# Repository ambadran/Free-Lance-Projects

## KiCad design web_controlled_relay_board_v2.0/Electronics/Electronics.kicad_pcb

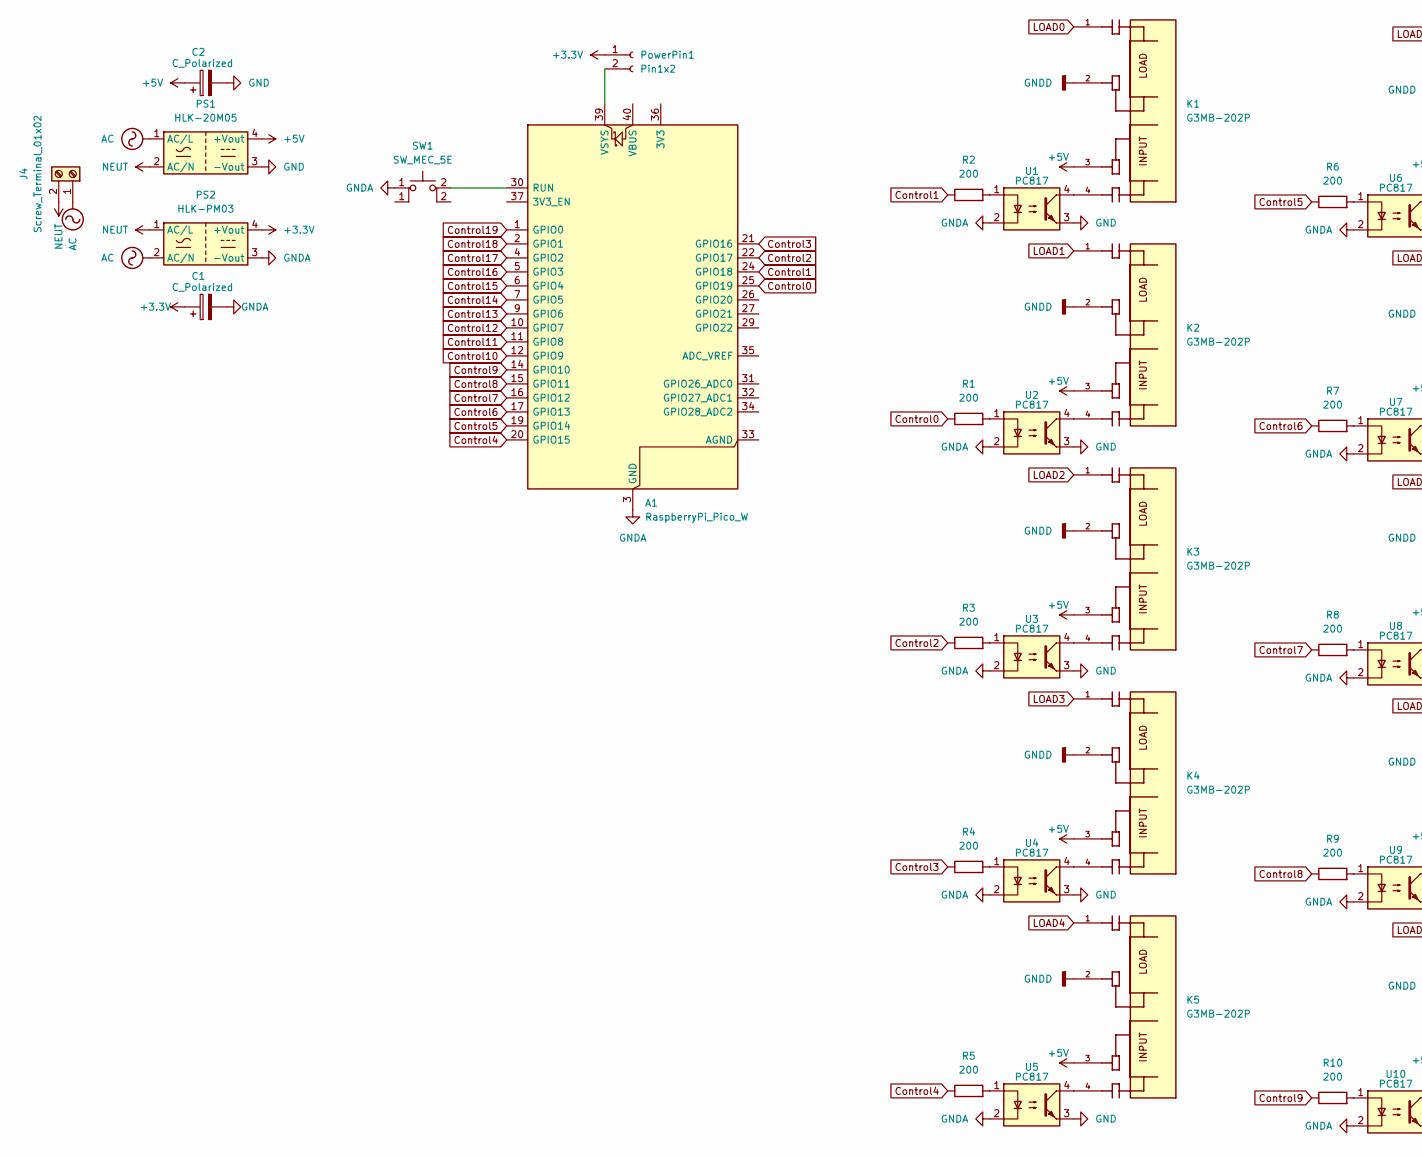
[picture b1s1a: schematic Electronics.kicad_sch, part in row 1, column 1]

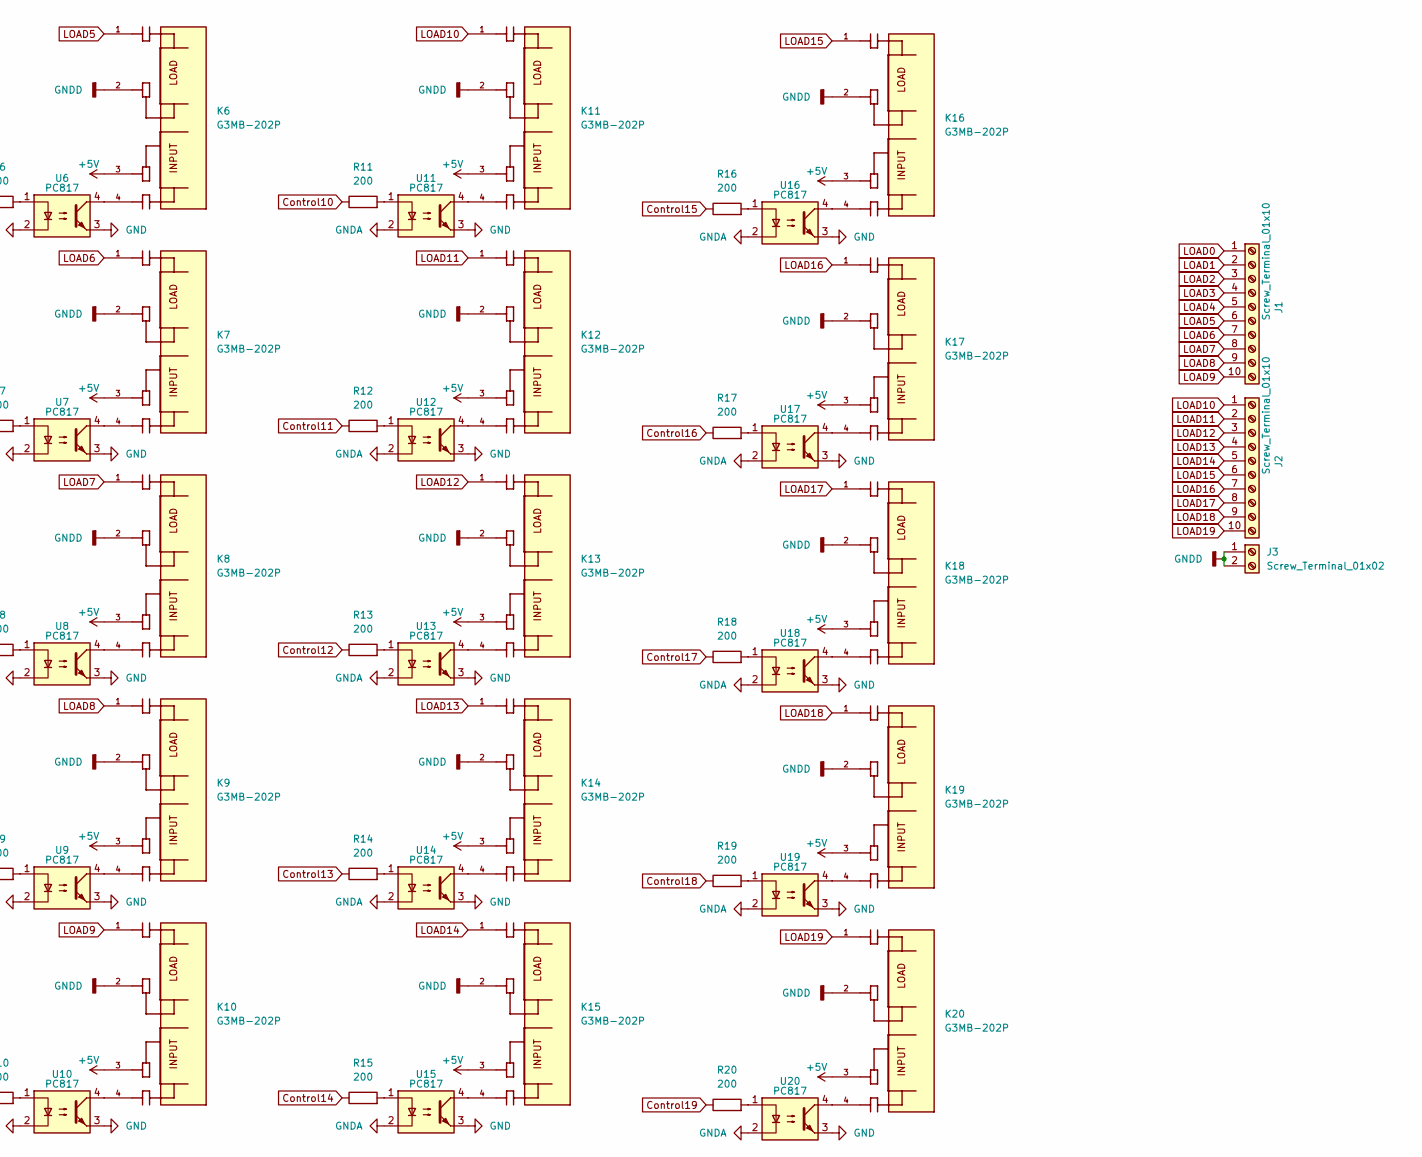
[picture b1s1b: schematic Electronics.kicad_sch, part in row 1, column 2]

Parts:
A1: RaspberryPi_Pico_W; RaspberryPi_Pico_Common_THT
C1: C_Polarized; CP_Radial_D6.3mm_P2.50mm
C2: C_Polarized; CP_Radial_D8.0mm_P3.50mm
J1, J2: Screw_Terminal_01x10; TerminalBlock_CUI_TB007-508-10_1x10_P5.08mm_Horizontal
J3, J4: Screw_Terminal_01x02; TerminalBlock_bornier-2_P5.08mm
K1, K2, K3, K4, K5, K6, K7, K8, K9, K10, K11, K12, K13, K14, K15, K16, K17, K18, K19, K20: G3MB-202P; RELAY_G3MB-202P; PARTREV J091-E1-1A
PS1: HLK-20M05; Converter_ACDC_Hi-Link_HLK-20Mxx
PS2: HLK-PM03; Converter_ACDC_Hi-Link_HLK-PMxx
PowerPin1: Pin1x2; PinSocket_1x02_P2.54mm_Vertical
R1, R2, R3, R4, R5, R6, R7, R8, R9, R10, R11, R12, R13, R14, R15, R16, R17, R18, R19, R20: 200; R_Axial_DIN0207_L6.3mm_D2.5mm_P7.62mm_Horizontal
SW1: SW_MEC_5E; SW_PUSH_6mm
U1, U2, U3, U4, U5, U6, U7, U8, U9, U10, U11, U12, U13, U14, U15, U16, U17, U18, U19, U20: PC817; DIP-4_W7.62mm

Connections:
+3.3V: C1.1, PS2.4 (+Vout), PowerPin1.1
+5V: C2.1, K1.3, K2.3, K3.3, K4.3, K5.3, K6.3, K7.3, K8.3, K9.3, K10.3, K11.3, K12.3, K13.3, K14.3, K15.3, K16.3, K17.3, K18.3, K19.3, K20.3, PS1.4 (+Vout)
AC: J4.1, PS1.1 (AC/L), PS2.2 (AC/N)
Control0: A1.25 (GPIO19), R1.1
Control1: A1.24 (GPIO18), R2.1
Control2: A1.22 (GPIO17), R3.1
Control3: A1.21 (GPIO16), R4.1
Control4: A1.20 (GPIO15), R5.1
Control5: A1.19 (GPIO14), R6.1
Control6: A1.17 (GPIO13), R7.1
Control7: A1.16 (GPIO12), R8.1
Control8: A1.15 (GPIO11), R9.1
Control9: A1.14 (GPIO10), R10.1
Control10: A1.12 (GPIO9), R11.1
Control11: A1.11 (GPIO8), R12.1
Control12: A1.10 (GPIO7), R13.1
Control13: A1.9 (GPIO6), R14.1
Control14: A1.7 (GPIO5), R15.1
Control15: A1.6 (GPIO4), R16.1
Control16: A1.5 (GPIO3), R17.1
Control17: A1.4 (GPIO2), R18.1
Control18: A1.2 (GPIO1), R19.1
Control19: A1.1 (GPIO0), R20.1
GND: C2.2, PS1.3 (-Vout), U1.3, U2.3, U3.3, U4.3, U5.3, U6.3, U7.3, U8.3, U9.3, U10.3, U11.3, U12.3, U13.3, U14.3, U15.3, U16.3, U17.3, U18.3, U19.3, U20.3
GNDA: A1.3 (GND), A1.8 (GND), A1.13 (GND), A1.18 (GND), A1.23 (GND), A1.28 (GND), A1.38 (GND), C1.2, PS2.3 (-Vout), SW1.1, U1.2, U2.2, U3.2, U4.2, U5.2, U6.2, U7.2, U8.2, U9.2, U10.2, U11.2, U12.2, U13.2, U14.2, U15.2, U16.2, U17.2, U18.2, U19.2, U20.2
GNDD: J3.1, J3.2, K1.2, K2.2, K3.2, K4.2, K5.2, K6.2, K7.2, K8.2, K9.2, K10.2, K11.2, K12.2, K13.2, K14.2, K15.2, K16.2, K17.2, K18.2, K19.2, K20.2
LOAD0: J1.1, K1.1
LOAD1: J1.2, K2.1
LOAD2: J1.3, K3.1
LOAD3: J1.4, K4.1
LOAD4: J1.5, K5.1
LOAD5: J1.6, K6.1
LOAD6: J1.7, K7.1
LOAD7: J1.8, K8.1
LOAD8: J1.9, K9.1
LOAD9: J1.10, K10.1
LOAD10: J2.1, K11.1
LOAD11: J2.2, K12.1
LOAD12: J2.3, K13.1
LOAD13: J2.4, K14.1
LOAD14: J2.5, K15.1
LOAD15: J2.6, K16.1
LOAD16: J2.7, K17.1
LOAD17: J2.8, K18.1
LOAD18: J2.9, K19.1
LOAD19: J2.10, K20.1
NEUT: J4.2, PS1.2 (AC/N), PS2.1 (AC/L)
unnamed: A1.30 (RUN), SW1.2
unnamed: A1.39 (VSYS), PowerPin1.2
unnamed: K1.4, U1.4
unnamed: K2.4, U2.4
unnamed: K3.4, U3.4
unnamed: K4.4, U4.4
unnamed: K5.4, U5.4
unnamed: K6.4, U6.4
unnamed: K7.4, U7.4
unnamed: K8.4, U8.4
unnamed: K9.4, U9.4
unnamed: K10.4, U10.4
unnamed: K11.4, U11.4
unnamed: K12.4, U12.4
unnamed: K13.4, U13.4
unnamed: K14.4, U14.4
unnamed: K15.4, U15.4
unnamed: K16.4, U16.4
unnamed: K17.4, U17.4
unnamed: K18.4, U18.4
unnamed: K19.4, U19.4
unnamed: K20.4, U20.4
unnamed: R1.2, U2.1
unnamed: R2.2, U1.1
unnamed: R3.2, U3.1
unnamed: R4.2, U4.1
unnamed: R5.2, U5.1
unnamed: R6.2, U6.1
unnamed: R7.2, U7.1
unnamed: R8.2, U8.1
unnamed: R9.2, U9.1
unnamed: R10.2, U10.1
unnamed: R11.2, U11.1
unnamed: R12.2, U12.1
unnamed: R13.2, U13.1
unnamed: R14.2, U14.1
unnamed: R15.2, U15.1
unnamed: R16.2, U16.1
unnamed: R17.2, U17.1
unnamed: R18.2, U18.1
unnamed: R19.2, U19.1
unnamed: R20.2, U20.1

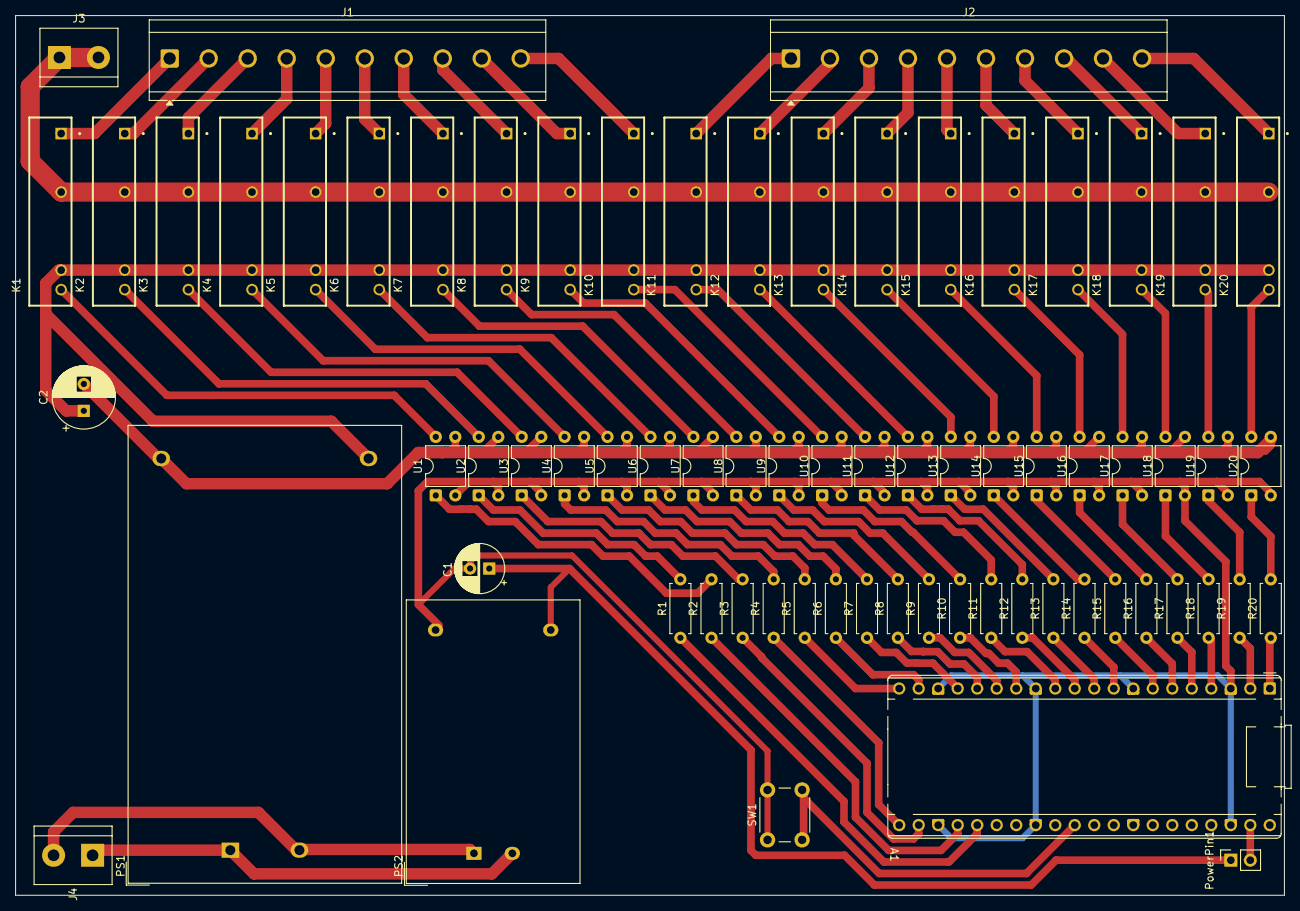
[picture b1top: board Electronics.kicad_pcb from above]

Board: 2 copper layers, 165.2 x 114.6 mm, 71 parts (0 on the bottom side), 89 nets.

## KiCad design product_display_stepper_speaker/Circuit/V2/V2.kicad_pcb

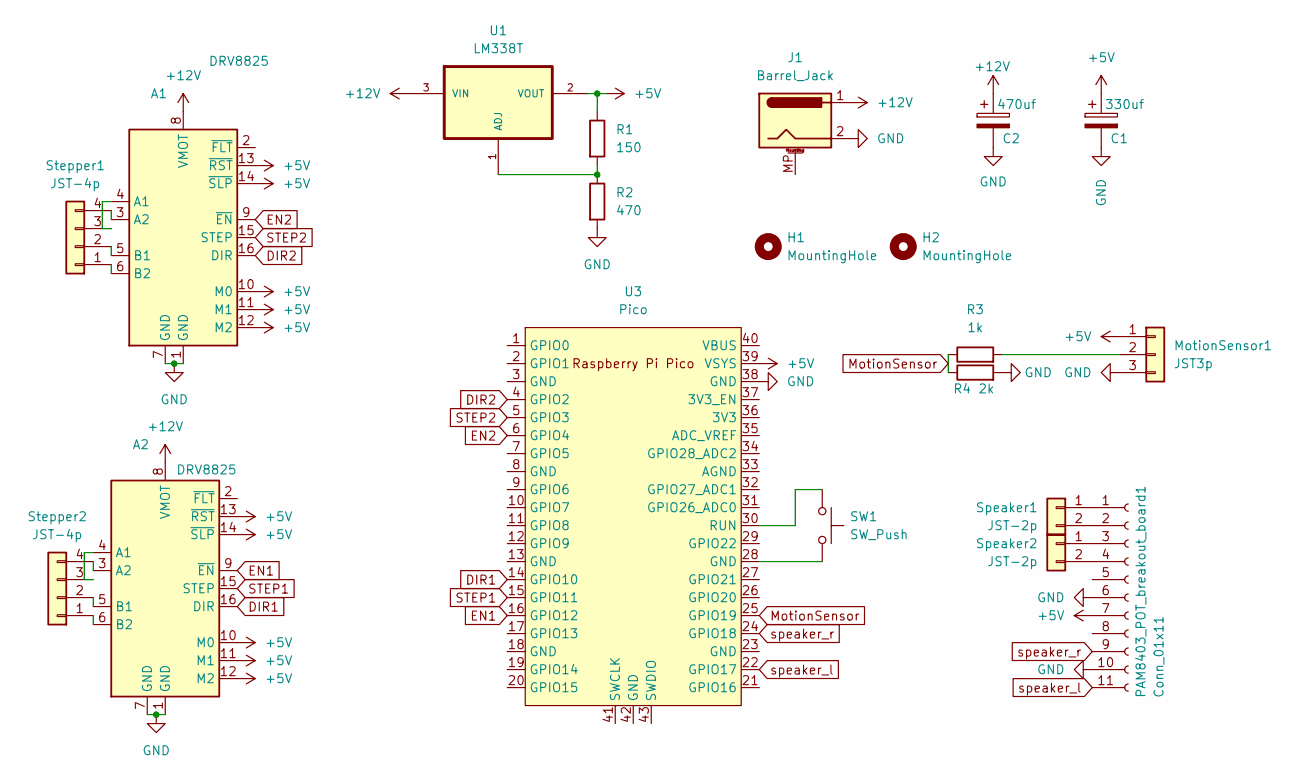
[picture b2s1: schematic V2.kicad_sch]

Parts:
A1, A2: DRV8825; DRV8825_module
C1: 330uf; C_Radial_D8.0mm_H11.5mm_P3.50mm
C2: 470uf; C_Radial_D8.0mm_H11.5mm_P3.50mm
H1, H2: MountingHole; MountingHole_3.2mm_M3
J1: Barrel_Jack; BarrelJack_GCT_DCJ200-10-A_Horizontal
MotionSensor1: JST3p; JST_EH_B3B-EH-A_1x03_P2.50mm_Vertical
PAM8403_POT_breakout_board1: Conn_01x11; PinHeader_1x11_P2.54mm_Vertical
R1: 150; R_Axial_DIN0207_L6.3mm_D2.5mm_P7.62mm_Horizontal
R2: 470; R_Axial_DIN0207_L6.3mm_D2.5mm_P7.62mm_Horizontal
R3: 1k; R_Axial_DIN0207_L6.3mm_D2.5mm_P7.62mm_Horizontal
R4: 2k; R_Axial_DIN0207_L6.3mm_D2.5mm_P7.62mm_Horizontal
SW1: SW_Push; SW_PUSH_6mm
Speaker1, Speaker2: JST-2p; JST_EH_B2B-EH-A_1x02_P2.50mm_Vertical
Stepper1, Stepper2: JST-4p; JST_EH_B4B-EH-A_1x04_P2.50mm_Vertical
U1: LM338T; TO254P1054X470X1955-3
U3: Pico; RPi_Pico_SMD_TH

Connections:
+5V: A1.10 (M0), A1.11 (M1), A1.12 (M2), A1.13 (~RST), A1.14 (~SLP), A2.10 (M0), A2.11 (M1), A2.12 (M2), A2.13 (~RST), A2.14 (~SLP), C1.1, MotionSensor1.1, PAM8403_POT_breakout_board1.7, R1.1, U1.2 (VOUT), U3.39 (VSYS)
+12V: A1.8 (VMOT), A2.8 (VMOT), C2.1, J1.1, U1.3 (VIN)
DIR1: A2.16 (DIR), U3.14 (GPIO10)
DIR2: A1.16 (DIR), U3.4 (GPIO2)
EN1: A2.9 (~EN), U3.16 (GPIO12)
EN2: A1.9 (~EN), U3.6 (GPIO4)
GND: A1.1 (GND), A1.7 (GND), A2.1 (GND), A2.7 (GND), C1.2, C2.2, J1.2, MotionSensor1.3, PAM8403_POT_breakout_board1.6, PAM8403_POT_breakout_board1.10, R2.2, R4.2, U3.38 (GND)
MotionSensor: R3.1, R4.1, U3.25 (GPIO19)
unnamed: A1.4 (A1), Stepper1.3
unnamed: A1.3 (A2), Stepper1.4
unnamed: A1.5 (B1), Stepper1.2
unnamed: A1.6 (B2), Stepper1.1
unnamed: A2.4 (A1), Stepper2.3
unnamed: A2.3 (A2), Stepper2.4
unnamed: A2.5 (B1), Stepper2.2
unnamed: A2.6 (B2), Stepper2.1
unnamed: MotionSensor1.2, R3.2
unnamed: PAM8403_POT_breakout_board1.1, Speaker1.1
unnamed: PAM8403_POT_breakout_board1.2, Speaker1.2
unnamed: PAM8403_POT_breakout_board1.3, Speaker2.1
unnamed: PAM8403_POT_breakout_board1.4, Speaker2.2
unnamed: SW1.2, U3.28 (GND)
unnamed: R1.2, R2.1, U1.1 (ADJ)
unnamed: SW1.1, U3.30 (RUN)
STEP1: A2.15 (STEP), U3.15 (GPIO11)
STEP2: A1.15 (STEP), U3.5 (GPIO3)
speaker_l: PAM8403_POT_breakout_board1.11, U3.22 (GPIO17)
speaker_r: PAM8403_POT_breakout_board1.9, U3.24 (GPIO18)

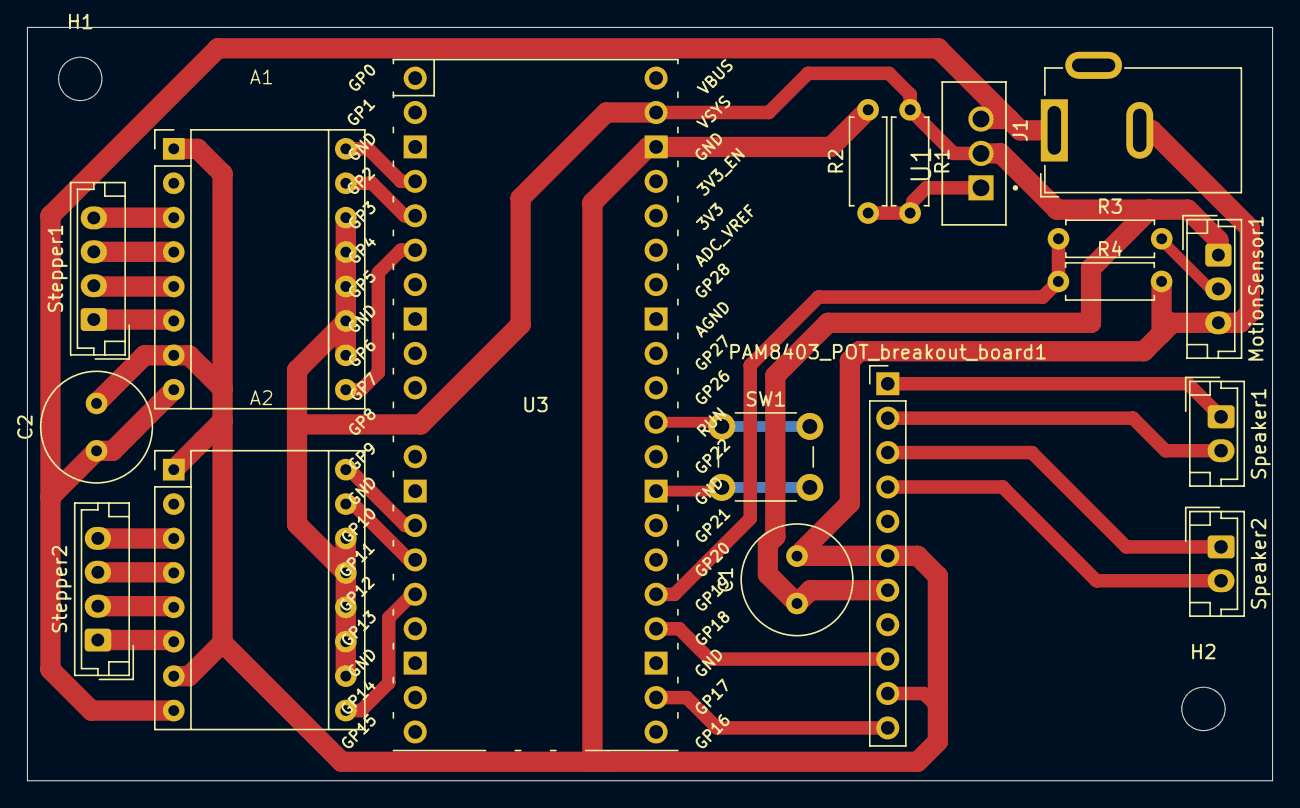
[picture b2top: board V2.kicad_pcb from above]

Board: 2 copper layers, 91.9 x 55.6 mm, 20 parts (0 on the bottom side), 28 nets.

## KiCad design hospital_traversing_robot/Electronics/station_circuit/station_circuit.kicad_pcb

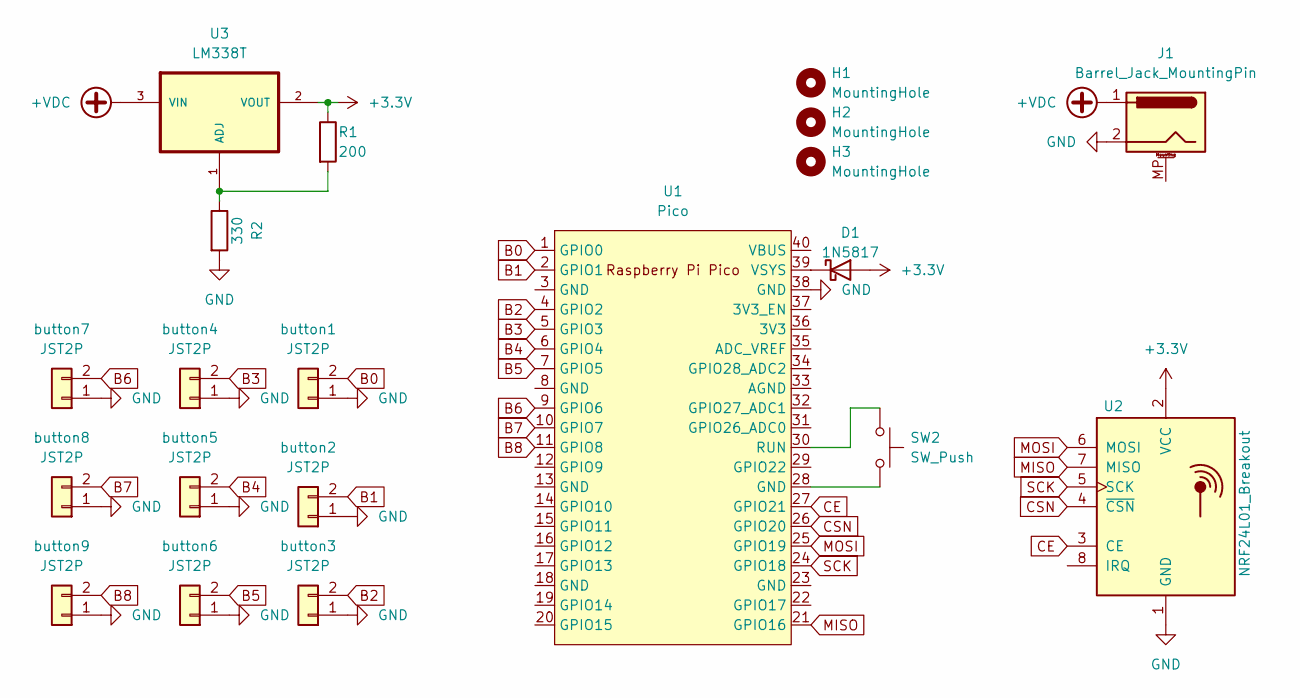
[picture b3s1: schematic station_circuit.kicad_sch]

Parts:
D1: 1N5817; D_DO-41_SOD81_P10.16mm_Horizontal
H1, H2, H3: MountingHole; MountingHole_3.2mm_M3
J1: Barrel_Jack_MountingPin; BarrelJack_GCT_DCJ200-10-A_Horizontal
R1: 200; R_Axial_DIN0207_L6.3mm_D2.5mm_P7.62mm_Horizontal
R2: 330; R_Axial_DIN0207_L6.3mm_D2.5mm_P7.62mm_Horizontal
SW2: SW_Push; SW_PUSH_6mm
U1: Pico; RPi_Pico_SMD_TH
U2: NRF24L01_Breakout; nRF24L01_Breakout
U3: LM338T; TO254P1054X470X1955-3
button1, button2, button3, button4, button5, button6, button7, button8, button9: JST2P; JST_EH_B2B-EH-A_1x02_P2.50mm_Vertical

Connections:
+3.3V: D1.2 (A), R1.1, U2.2 (VCC), U3.2 (VOUT)
+VDC: J1.1, U3.3 (VIN)
B0: U1.1 (GPIO0), button1.2
B1: U1.2 (GPIO1), button2.2
B2: U1.4 (GPIO2), button3.2
B3: U1.5 (GPIO3), button4.2
B4: U1.6 (GPIO4), button5.2
B5: U1.7 (GPIO5), button6.2
B6: U1.9 (GPIO6), button7.2
B7: U1.10 (GPIO7), button8.2
B8: U1.11 (GPIO8), button9.2
CE: U1.27 (GPIO21), U2.3 (CE)
CSN: U1.26 (GPIO20), U2.4 (~CSN)
GND: J1.2, R2.2, U1.38 (GND), U2.1 (GND), button1.1, button2.1, button3.1, button4.1, button5.1, button6.1, button7.1, button8.1, button9.1
MISO: U1.21 (GPIO16), U2.7 (MISO)
MOSI: U1.25 (GPIO19), U2.6 (MOSI)
unnamed: D1.1 (K), U1.39 (VSYS)
unnamed: SW2.2, U1.28 (GND)
unnamed: SW2.1, U1.30 (RUN)
unnamed: R1.2, R2.1, U3.1 (ADJ)
SCK: U1.24 (GPIO18), U2.5 (SCK)

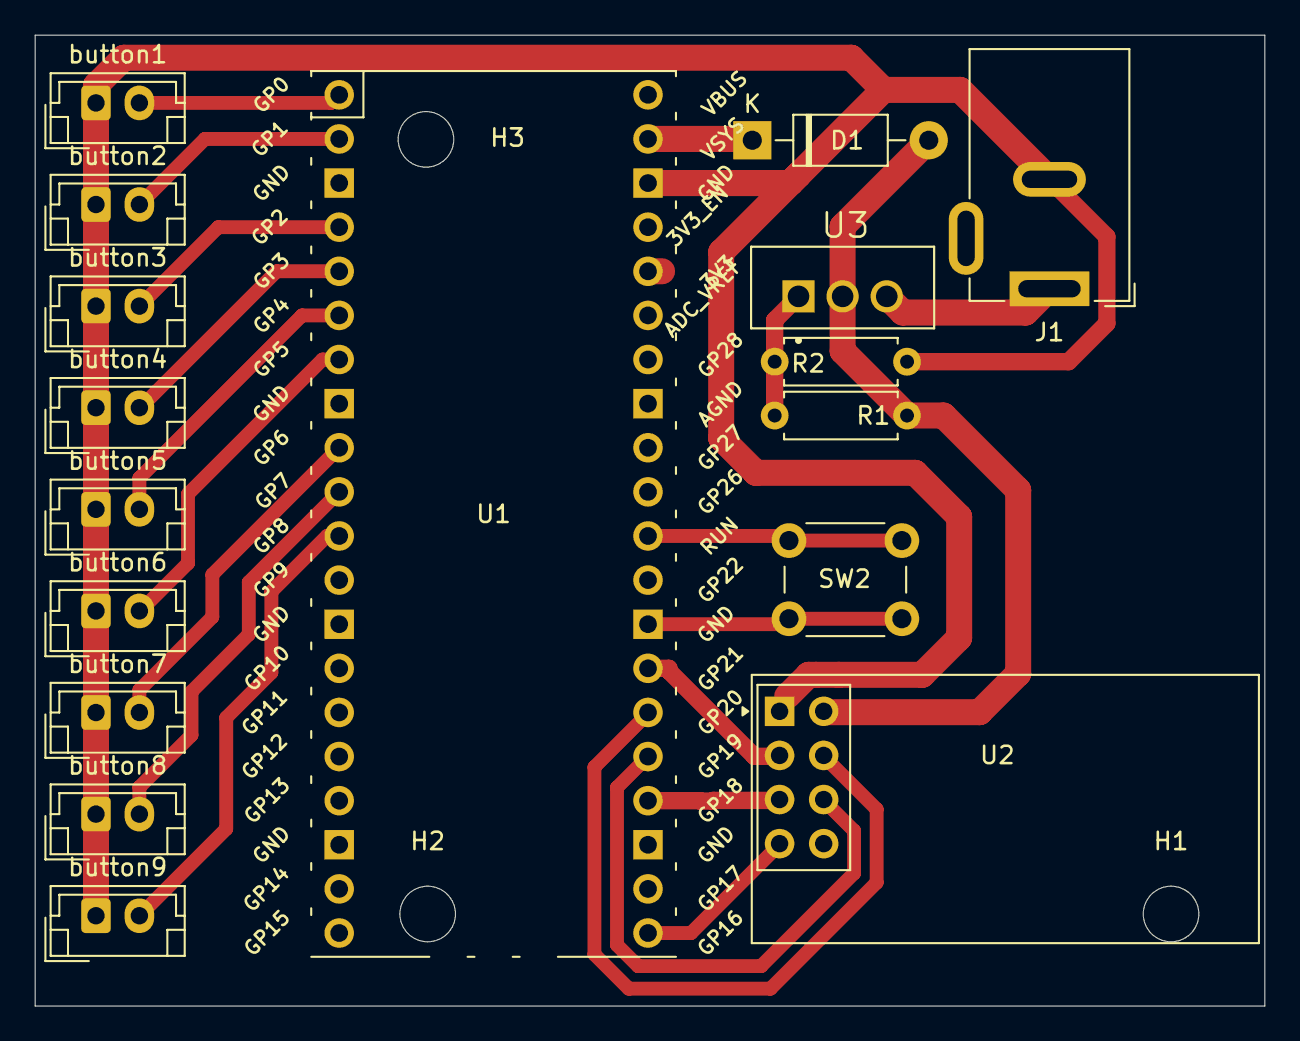
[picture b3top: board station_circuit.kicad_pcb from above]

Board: 2 copper layers, 70.8 x 55.9 mm, 20 parts (0 on the bottom side), 21 nets.

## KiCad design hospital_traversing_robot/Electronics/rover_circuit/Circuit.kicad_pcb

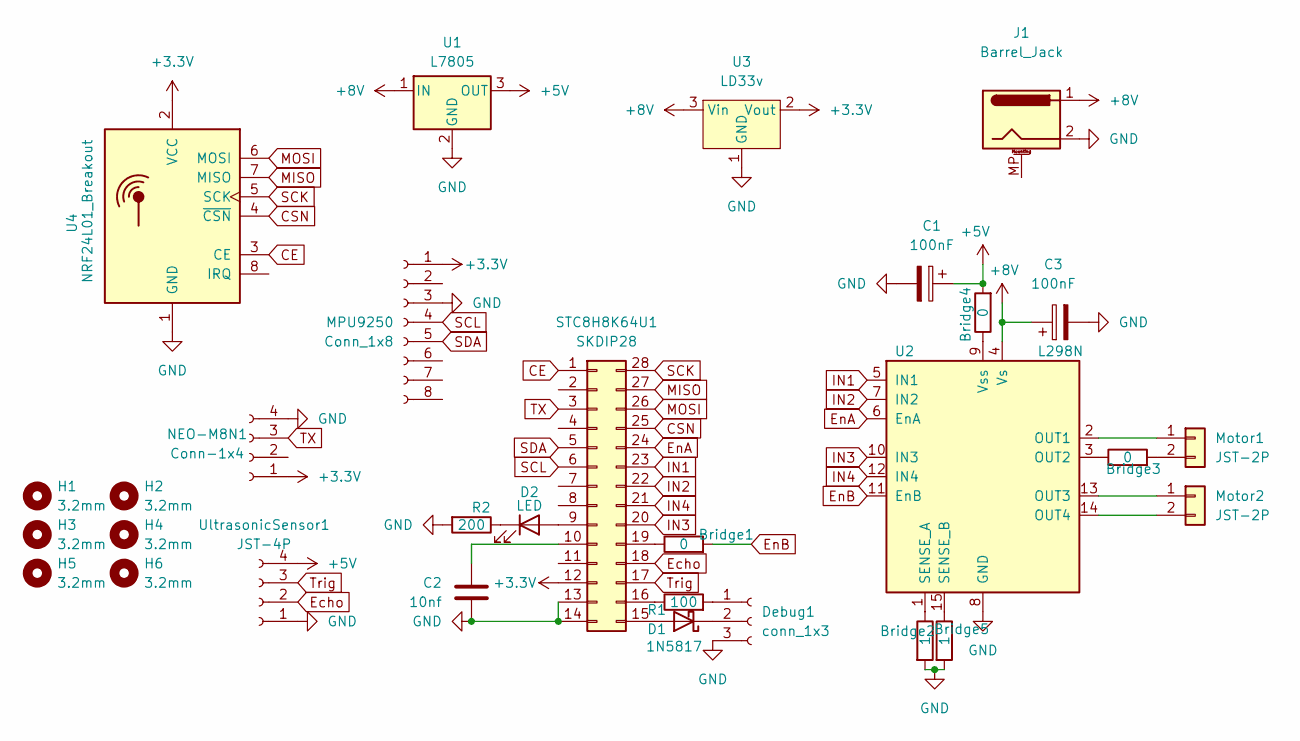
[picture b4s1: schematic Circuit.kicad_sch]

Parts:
Bridge1: 0; R_Axial_DIN0207_L6.3mm_D2.5mm_P7.62mm_Horizontal
Bridge2: 1; R_Axial_DIN0207_L6.3mm_D2.5mm_P10.16mm_Horizontal
Bridge3: 0; R_Axial_DIN0204_L3.6mm_D1.6mm_P7.62mm_Horizontal
Bridge4: 0; R_Axial_DIN0207_L6.3mm_D2.5mm_P15.24mm_Horizontal
Bridge5: 1; R_Axial_DIN0207_L6.3mm_D2.5mm_P7.62mm_Horizontal
C1, C3: 100nF; CP_Radial_D5.0mm_P2.50mm
C2: 10nf; C_Disc_D4.3mm_W1.9mm_P5.00mm
D1: 1N5817; D_DO-41_SOD81_P7.62mm_Horizontal
D2: LED; LED_D5.0mm
Debug1: conn_1x3; PinHeader_1x03_P2.54mm_Vertical
H1, H2, H3, H4, H5, H6: 3.2mm; MountingHole_3.2mm_M3_DIN965
J1: Barrel_Jack; BarrelJack_Wuerth_6941xx301002
MPU9250: Conn_1x8; PinHeader_1x08_P2.54mm_Vertical
Motor1, Motor2: JST-2P; JST_EH_B2B-EH-A_1x02_P2.50mm_Vertical
NEO-M8N1: Conn-1x4; PinHeader_1x04_P2.54mm_Vertical
R1: 100; R_Axial_DIN0207_L6.3mm_D2.5mm_P7.62mm_Horizontal
R2: 200; R_Axial_DIN0207_L6.3mm_D2.5mm_P7.62mm_Horizontal
STC8H8K64U1: SKDIP28; DIP-28_W7.62mm_LongPads
U1: L7805; TO-220-3_Vertical
U2: L298N; TO-220-15_P2.54x2.54mm_StaggerOdd_Lead4.58mm_Vertical
U3: LD33v; TO-220-3_Vertical
U4: NRF24L01_Breakout; nRF24L01_Breakout
UltrasonicSensor1: JST-4P; JST_EH_B4B-EH-A_1x04_P2.50mm_Vertical

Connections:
+3.3V: MPU9250.1, NEO-M8N1.1, STC8H8K64U1.12, U3.2 (Vout), U4.2 (VCC)
+5V: Bridge4.2, C1.1, U1.3 (OUT), UltrasonicSensor1.4
+8V: C3.1, J1.1, U1.1 (IN), U2.4 (Vs), U3.3 (Vin)
CE: STC8H8K64U1.1, U4.3 (CE)
CSN: STC8H8K64U1.25, U4.4 (~CSN)
Echo: STC8H8K64U1.18, UltrasonicSensor1.2
EnA: STC8H8K64U1.24, U2.6 (EnA)
EnB: Bridge1.2, U2.11 (EnB)
GND: Bridge2.2, Bridge5.2, C1.2, C2.2, C3.2, Debug1.3, J1.2, MPU9250.3, NEO-M8N1.4, R2.2, STC8H8K64U1.13, STC8H8K64U1.14, U1.2 (GND), U2.8 (GND), U3.1 (GND), U4.1 (GND), UltrasonicSensor1.1
IN1: STC8H8K64U1.23, U2.5 (IN1)
IN2: STC8H8K64U1.22, U2.7 (IN2)
IN3: STC8H8K64U1.20, U2.10 (IN3)
IN4: STC8H8K64U1.21, U2.12 (IN4)
MISO: STC8H8K64U1.27, U4.7 (MISO)
MOSI: STC8H8K64U1.26, U4.6 (MOSI)
unnamed: D1.2 (A), STC8H8K64U1.15
unnamed: D1.1 (K), Debug1.2
unnamed: D2.2 (A), STC8H8K64U1.9
unnamed: D2.1 (K), R2.1
unnamed: Debug1.1, R1.2
unnamed: Motor1.1, U2.2 (OUT1)
unnamed: Bridge3.2, Motor1.2
unnamed: Motor2.1, U2.13 (OUT3)
unnamed: Motor2.2, U2.14 (OUT4)
unnamed: C2.1, STC8H8K64U1.10
unnamed: R1.1, STC8H8K64U1.16
unnamed: Bridge1.1, STC8H8K64U1.19
unnamed: Bridge3.1, U2.3 (OUT2)
unnamed: Bridge2.1, U2.1 (SENSE_A)
unnamed: Bridge5.1, U2.15 (SENSE_B)
unnamed: Bridge4.1, U2.9 (Vss)
SCK: STC8H8K64U1.28, U4.5 (SCK)
SCL: MPU9250.4, STC8H8K64U1.6
SDA: MPU9250.5, STC8H8K64U1.5
TX: NEO-M8N1.3, STC8H8K64U1.3
Trig: STC8H8K64U1.17, UltrasonicSensor1.3

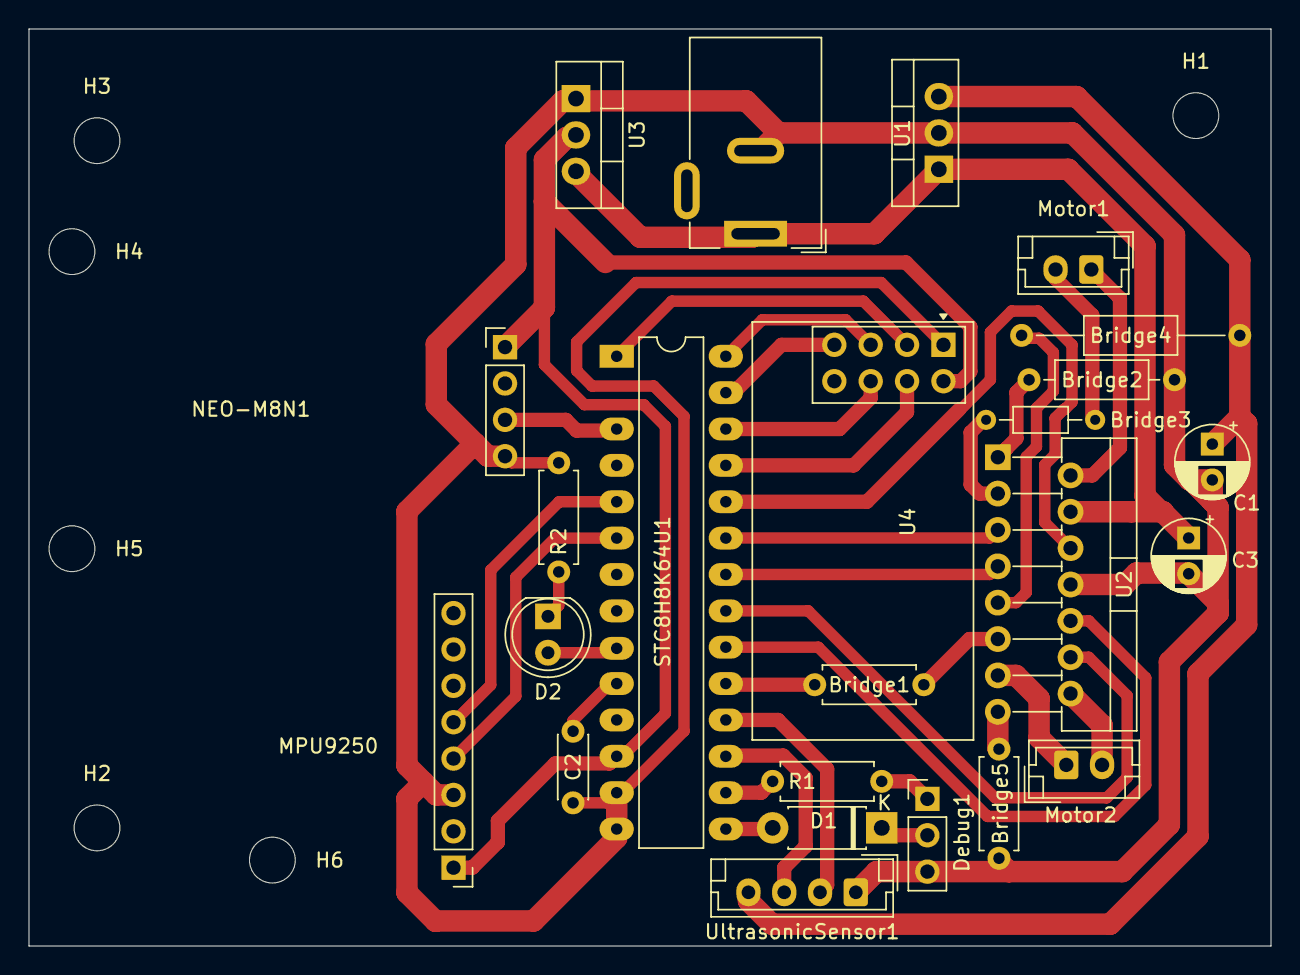
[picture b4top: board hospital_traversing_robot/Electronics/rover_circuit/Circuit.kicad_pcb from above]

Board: 2 copper layers, 86.8 x 64.0 mm, 30 parts (0 on the bottom side), 36 nets.

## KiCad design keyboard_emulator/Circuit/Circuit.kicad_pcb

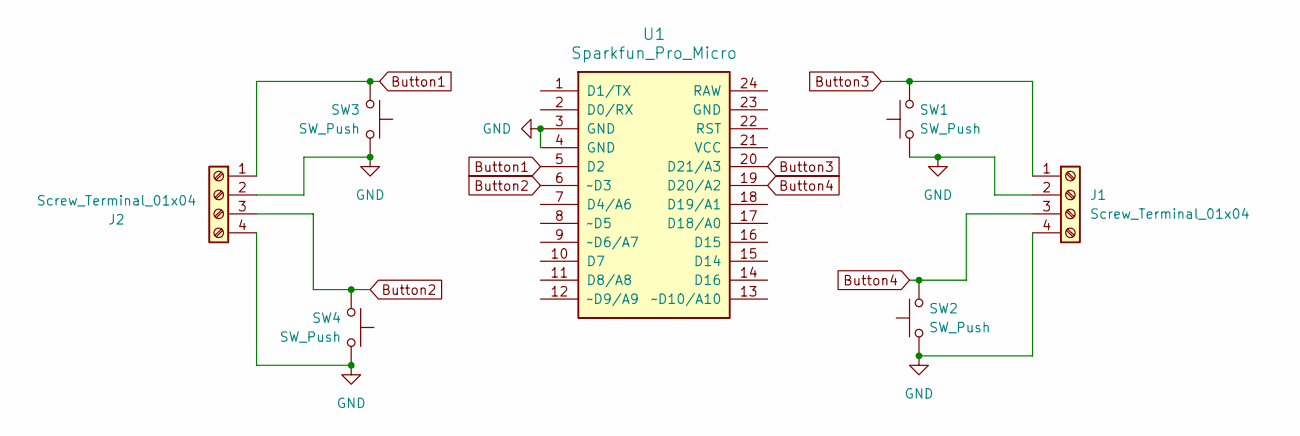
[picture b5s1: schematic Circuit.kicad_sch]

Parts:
J1, J2: Screw_Terminal_01x04; speaker_terminal_spring_4
SW1, SW2, SW3, SW4: SW_Push; push_button_oval
U1: Sparkfun_Pro_Micro

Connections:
Button1: J2.1, SW3.2, U1.5 (D2)
Button2: J2.3, SW4.2, U1.6 (~D3)
Button3: J1.1, SW1.2, U1.20 (D21/A3)
Button4: J1.3, SW2.2, U1.19 (D20/A2)
GND: J1.2, J1.4, J2.2, J2.4, SW1.1, SW2.1, SW3.1, SW4.1, U1.3 (GND), U1.4 (GND)

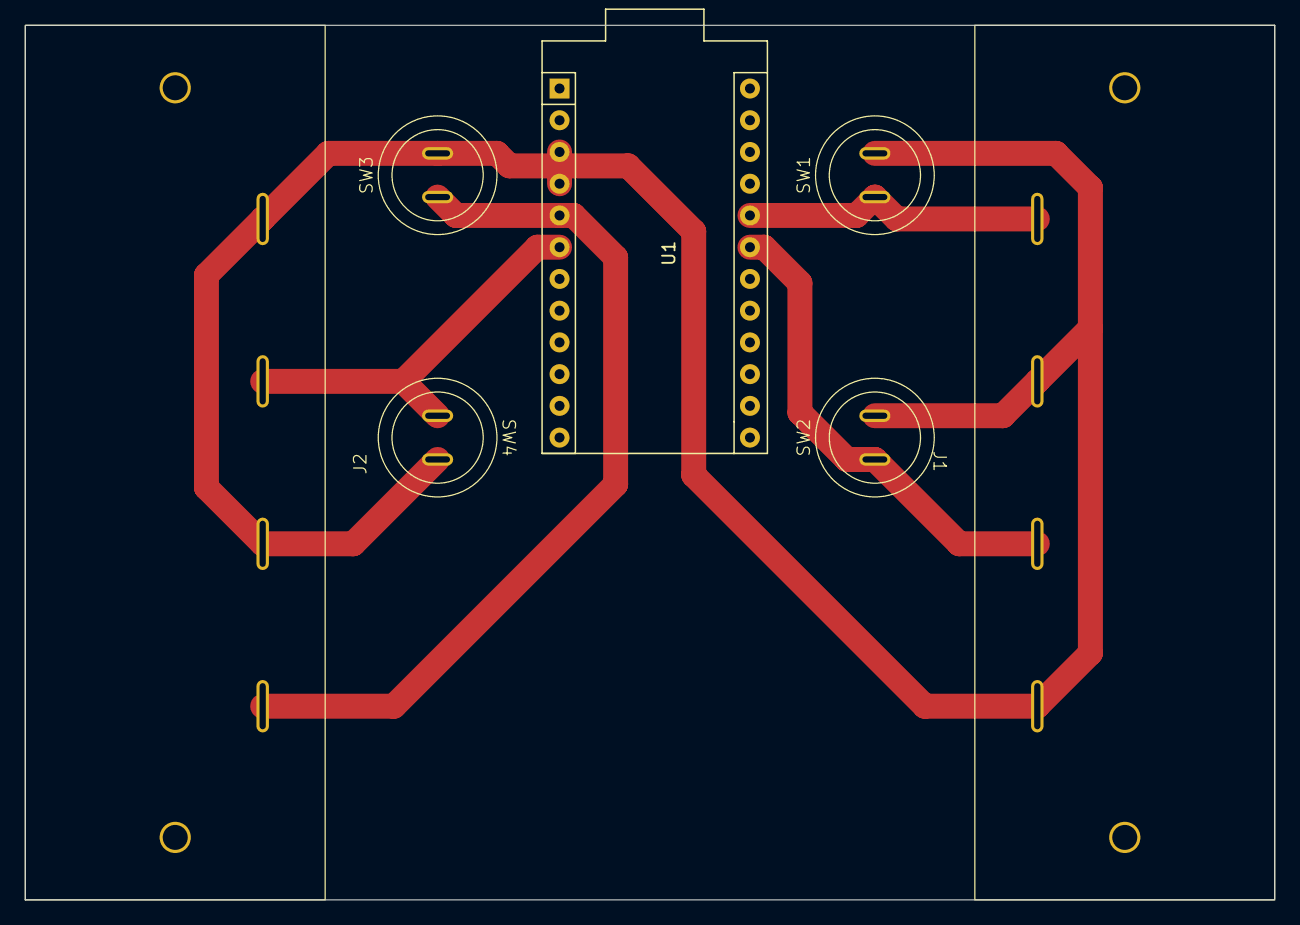
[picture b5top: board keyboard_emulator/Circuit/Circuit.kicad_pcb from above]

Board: 2 copper layers, 100.0 x 70.0 mm, 7 parts (0 on the bottom side), 5 nets.

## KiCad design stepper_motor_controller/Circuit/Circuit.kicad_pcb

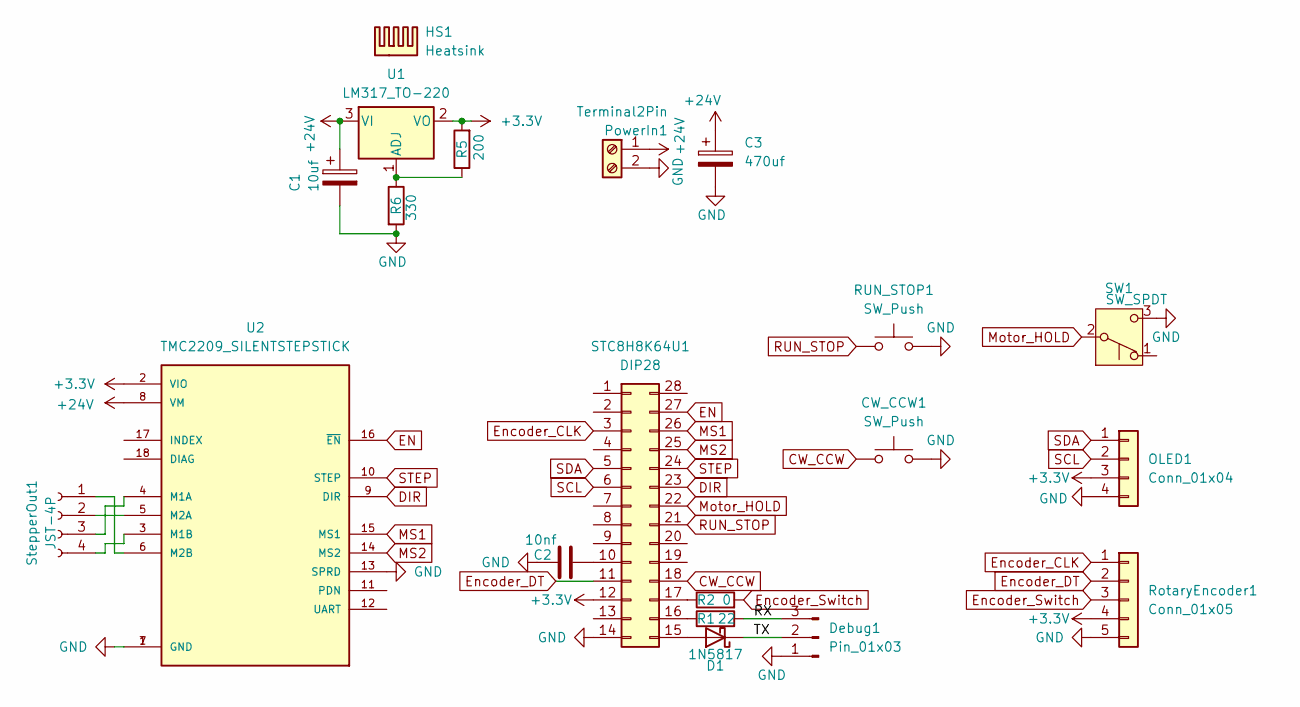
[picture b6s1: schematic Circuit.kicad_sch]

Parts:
C1: 10uf
C2: 10nf; R_Axial_DIN0207_L6.3mm_D2.5mm_P7.62mm_Horizontal
C3: 470uf
CW_CCW1: SW_Push; R_Axial_DIN0207_L6.3mm_D2.5mm_P5.08mm_Vertical
D1: 1N5817; D_DO-41_SOD81_P7.62mm_Horizontal
Debug1: Pin_01x03; PinHeader_1x03_P2.54mm_Vertical
HS1: Heatsink; Heatsink_Stonecold_HS-S01_13.21x6.35mm
OLED1: Conn_01x04; PinHeader_1x04_P2.54mm_Vertical
PowerIn1: Terminal2Pin; TerminalBlock_bornier-2_P5.08mm
R1: 22; R_Axial_DIN0207_L6.3mm_D2.5mm_P7.62mm_Horizontal
R2: 0; R_Axial_DIN0207_L6.3mm_D2.5mm_P7.62mm_Horizontal
R5: 200; R_Axial_DIN0207_L6.3mm_D2.5mm_P7.62mm_Horizontal
R6: 330; R_Axial_DIN0207_L6.3mm_D2.5mm_P7.62mm_Horizontal
RUN_STOP1: SW_Push; R_Axial_DIN0207_L6.3mm_D2.5mm_P5.08mm_Vertical
RotaryEncoder1: Conn_01x05; PinHeader_1x05_P2.54mm_Vertical
STC8H8K64U1: DIP28; DIP-28_W7.62mm_Socket_LongPads
SW1: SW_SPDT; PinHeader_1x03_P2.54mm_Vertical
StepperOut1: JST-4P; JST_EH_B4B-EH-A_1x04_P2.50mm_Vertical
U1: LM317_TO-220; TO-220-3_Vertical
U2: TMC2209_SILENTSTEPSTICK; MODULE_TMC2209_SILENTSTEPSTICK; PARTREV 1.20

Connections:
+3.3V: OLED1.3, R5.2, RotaryEncoder1.4, STC8H8K64U1.12, U1.2 (VO), U2.2 (VIO)
+24V: C1.1, C3.1, PowerIn1.1, U1.3 (VI), U2.8 (VM)
/RX: Debug1.3, R1.2
/TX: D1.1 (K), Debug1.2
CW_CCW: CW_CCW1.2, STC8H8K64U1.18
DIR: STC8H8K64U1.23, U2.9 (DIR)
EN: STC8H8K64U1.27, U2.16 (~EN)
Encoder_CLK: RotaryEncoder1.1, STC8H8K64U1.3
Encoder_DT: RotaryEncoder1.2, STC8H8K64U1.11
Encoder_Switch: R2.2, RotaryEncoder1.3
GND: C1.2, C2.1, C3.2, CW_CCW1.1, Debug1.1, OLED1.4, PowerIn1.2, R6.2, RUN_STOP1.1, RotaryEncoder1.5, STC8H8K64U1.14, SW1.3 (C), U2.1 (GND), U2.7 (GND), U2.13 (SPRD)
MS1: STC8H8K64U1.26, U2.15 (MS1)
MS2: STC8H8K64U1.25, U2.14 (MS2)
Motor_HOLD: STC8H8K64U1.22, SW1.2 (B)
unnamed: D1.2 (A), STC8H8K64U1.15
unnamed: C2.2, STC8H8K64U1.10
unnamed: R1.1, STC8H8K64U1.16
unnamed: R2.1, STC8H8K64U1.17
unnamed: StepperOut1.1, U2.6 (M2B)
unnamed: StepperOut1.2, U2.5 (M2A)
unnamed: StepperOut1.3, U2.4 (M1A)
unnamed: StepperOut1.4, U2.3 (M1B)
unnamed: R5.1, R6.1, U1.1 (ADJ)
RUN_STOP: RUN_STOP1.2, STC8H8K64U1.21
SCL: OLED1.2, STC8H8K64U1.6
SDA: OLED1.1, STC8H8K64U1.5
STEP: STC8H8K64U1.24, U2.10 (STEP)

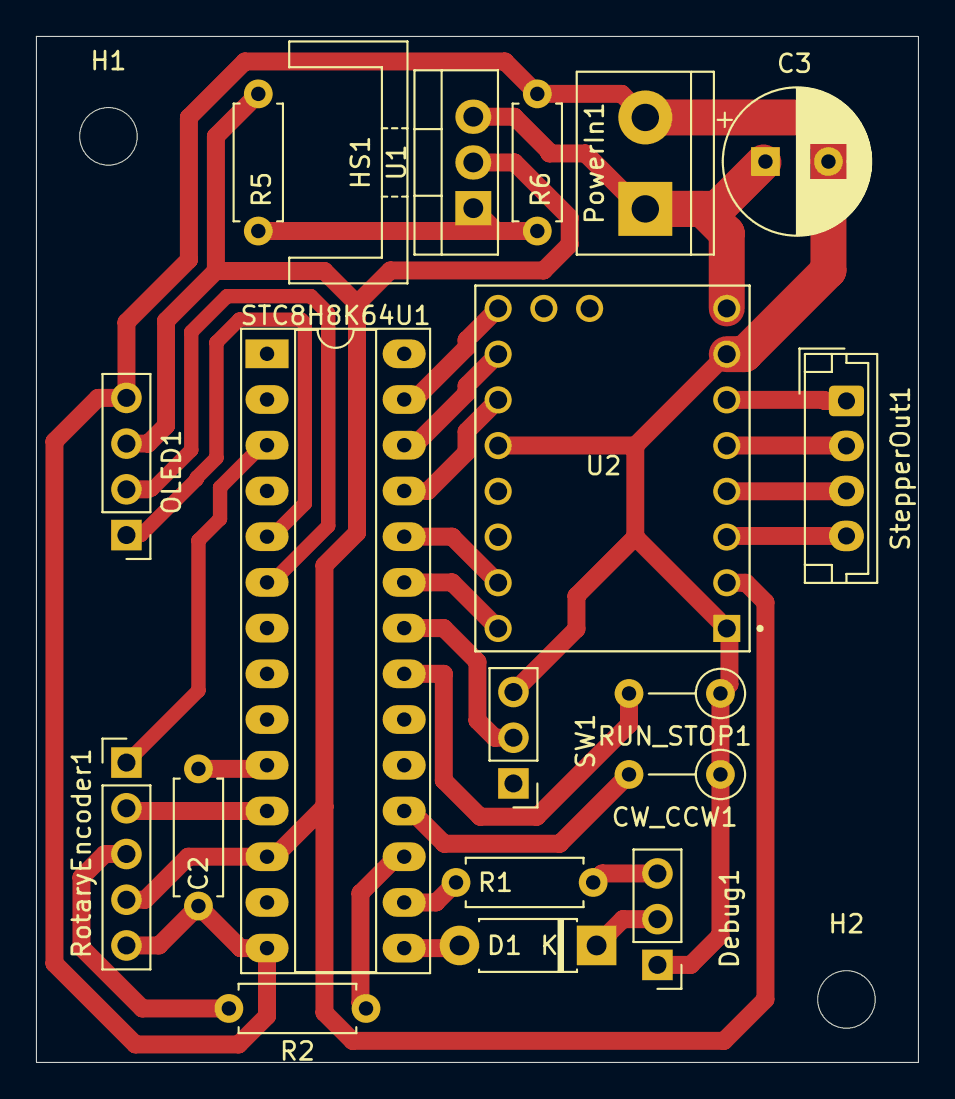
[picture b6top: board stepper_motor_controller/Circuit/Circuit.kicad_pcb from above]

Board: 2 copper layers, 49.0 x 57.0 mm, 21 parts (0 on the bottom side), 27 nets.

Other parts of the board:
H1, H2: 3.3mm; MountingHole_3.2mm_M3
